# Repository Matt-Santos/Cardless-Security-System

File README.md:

# Cardless Security System
***
## Project Description
A **cardless security system** based on human **electro cardiogram (ECG) biometrics** that will be able to identify specified individuals, assess their authorization privileges and subsequently permit or deny access to
restricted areas. The entry regulation method is a custom designed electronic door locking
mechanism. Device is includes additional security features to prevent unauthorized entry. The unit
itself is battery operated with audio and visual indicators used to denote various system states.

## Goals and Objectives
1) Differentiate between individuals based on personal ECG signals
2) A secure mechanical locking system driven by an electric motor
## Brief Background
Most biometric identification devices currently in use throughout the world rely on either facial,
fingerprint, retina, or voice recognition systems. All of these authentication methods have been shown to
produce unique signatures that remain relatively consistent over time and are difficult to emulate with
the notable exception of voice based systems. Although obviously less secure the appeal of audio
biometric systems is driven primarily by its substantially lower implementation costs as opposed to the
other metrics which require sophisticated vision hardware. This desire for inexpensive biometric devices
has driven the search for alternative unique human signatures. Over the last few years electrocardiogram
(ECG) based recognition has shown potential. One of the advantages of this metric include the fact it is
an internal signal which is highly subject to personal health and mental state and is thus difficult to
procure from unwilling or deceased individuals. It is also fairly inexpensive to both capture and process
the ECG signals leading to a very high overall desirability. Research into this field is still being
conducted and very few viable commercial products are currently available.

## Final Result
An enclosed printed circuit board mounted alongside a custom electronic door locking mechanism.
The board is to include a built-in ECG acquisition system, audio and visual status indicators, as well as
the internal processing power required to perform biometric identification.

## Timeline
See [Gantt Chart](/documents/reports/Proposal/ProjectSchedule.pdf)

# Software Listing
* Git
* KiCAD
* GanttProject
* Latex (MiKTeX)
* Matlab (Octave)
* LTSpice

# Team Members
* Matthew Santos
* Robert Goleberski
* Zuwei Li
# Supervisors
* Dr. Emadi
* Dr. Mirhassani

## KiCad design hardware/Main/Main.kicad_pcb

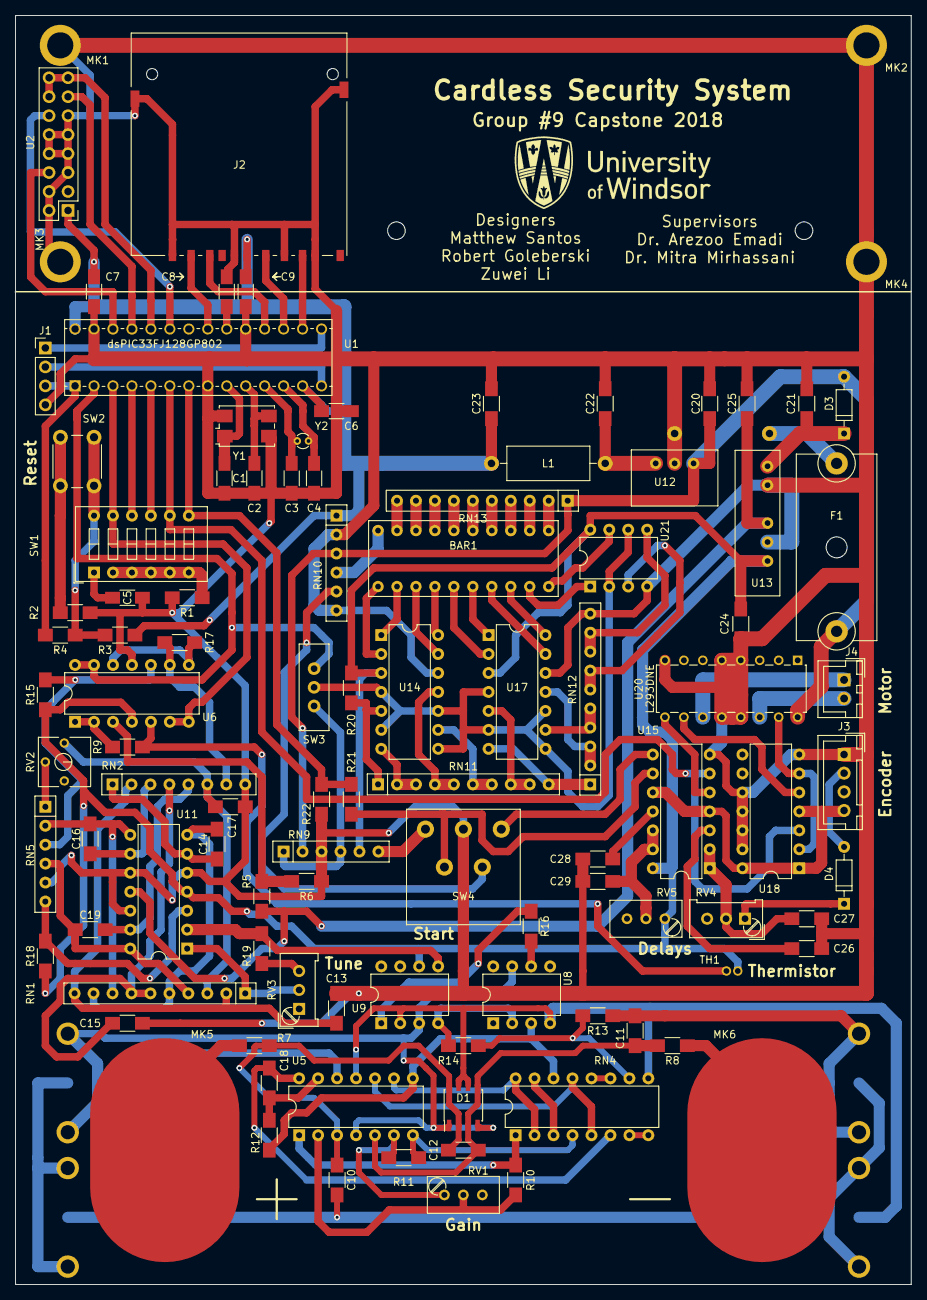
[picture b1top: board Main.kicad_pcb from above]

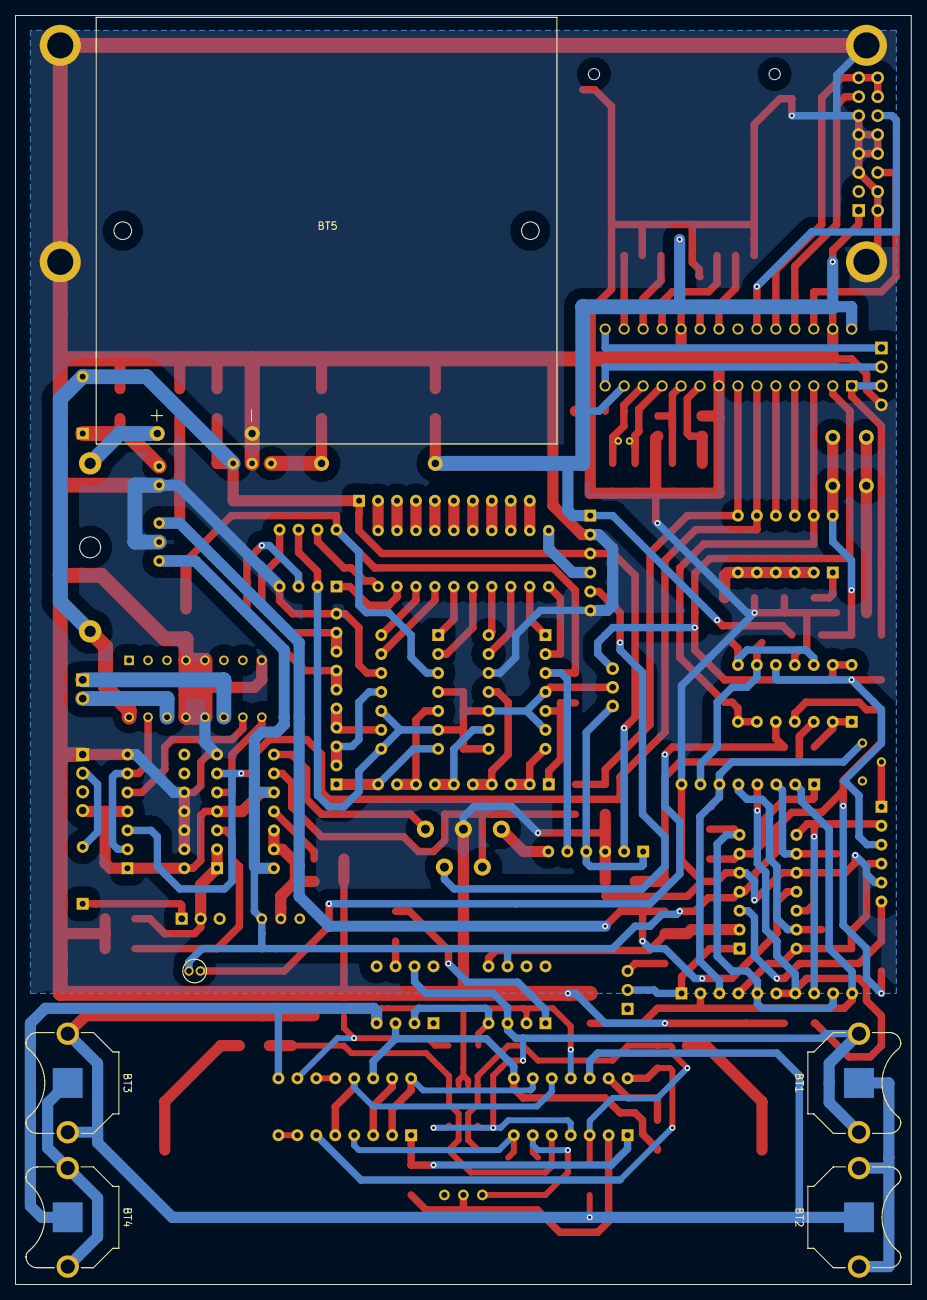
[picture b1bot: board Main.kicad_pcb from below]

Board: 2 copper layers, 120.0 x 170.0 mm, 108 parts (6 on the bottom side), 126 nets.

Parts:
BAR1: DC7G3HWA
BT1, BT2, BT3, BT4: Holder; Keystone_3001_1x12mm-CoinCell
BT5: Battery Holder; BH4AAPC
C1, C2: 27p; C1206C270F5GACTU
C3, C4: 15p; C1206C150J5GACTU
C5, C6, C7, C9: 0.1u; C1206C104K4RACTU
C8: 4.7u; F931C475KAA
C10, C11: 100p; R_1206_HandSoldering
C12: 1n; R_1206_HandSoldering
C13, C15, C17: 0.68u; R_1206_HandSoldering
C14, C16, C19: 0.068u; R_1206_HandSoldering
C18, C27, C29: 47u; R_1206_HandSoldering
C20, C22: 10u; R_1206_HandSoldering
C21, C24, C25: 4.7u; R_1206_HandSoldering
C23: 22u; R_1206_HandSoldering
C26, C28: 10n; R_1206_HandSoldering
D1: SMDA15TR; SOIC-8_3.9x4.9mm_Pitch1.27mm
D3, D4: 1N914; D_DO-35_SOD27_P7.62mm_Horizontal
F1: Fuse_Holder; 0031.8201
J1: ISCP; Pin_Header_Straight_1x04_Pitch2.54mm
J2: SD_Card; 145638009211859+
J3: EncoderHeader; JST_XH_B04B-XH-A_04x2.50mm_Straight
J4: MotorHeader; JST_XH_B02B-XH-A_02x2.50mm_Straight
L1: 10u; L_Axial_L11.0mm_D4.5mm_P15.24mm_Horizontal_Fastron_MECC
MK1, MK2, MK3, MK4: Mounting_Hole; MountingHole_2.5mm_Pad
MK5: Electrode_A; ECG_Pad
MK6: Electrode_B; ECG_Pad
R1, R4: 1k; R_1206_HandSoldering
R2, R16: 100; R_1206_HandSoldering
R3: 10k; R_1206_HandSoldering
R5: 5.6k; R_1206_HandSoldering
R6: 2.4k; R_1206_HandSoldering
R7, R8: 100k; R_1206_HandSoldering
R9: 3k; R_1206_HandSoldering
R10, R11, R19: 2k; R_1206_HandSoldering
R12: 82k; R_1206_HandSoldering
R13, R14: 1.5k; R_1206_HandSoldering
R15: 9k; R_1206_HandSoldering
R17: 40k; R_1206_HandSoldering
R18: 15k; R_1206_HandSoldering
R20: 18k; R_1206_HandSoldering
R21: 2.2k; R_1206_HandSoldering
R22: 3.3k; R_1206_HandSoldering
RN1: 3.3k; R_Array_SIP10
RN2: 10k; R_Array_SIP8
RN4: 10k; DIP-16_W7.62mm
RN5: 1k; R_Array_SIP6
RN9: 10k; R_Array_SIP6
RN10: 150; R_Array_SIP6
RN11, RN12: 2.7k; R_Array_SIP10
RN13: 150; R_Array_SIP10
RV1: 5kPOT; Potentiometer_Trimmer_Bourns_3296W
RV2: 3kPOT; 3362P-1-302LF
RV3: 2kPOT; Potentiometer_Trimmer_Bourns_PV36W
RV4: 100k POT; Potentiometer_Trimmer_Bourns_PV36W
RV5: 500k POT; Potentiometer_Trimmer_Bourns_3296W
SW1: SW_DIP_x06; 418117270906
SW2: Reset; TL1105F250Q
SW3: Bat-Test; EG1218
SW4: Start; UB15SKG035F-FF
TH1: Thermistor; DC103G9G
U1: dsPIC33FJ128GP802; DSPIC33FJ128GP802
U2: LCD_Header; Pin_Header_Straight_2x08_Pitch2.54mm
U5: LT1079CN; DIP-14_W7.62mm
U6, U11: TLC2264IN; DIP-14_W7.62mm
U8: LT1636; DIP-8_W7.62mm
U9: IL300; DIP-8_W7.62mm
U12: P7805-Q24-S3-S
U13: PDM1-S5-D5-S
U14, U17: LM339; DIP-14_W7.62mm
U15: NE556; DIP-14_W7.62mm
U18: 74HC74; DIP-14_W7.62mm
U20: L293DNE
U21: LM2903; DIP-8_W7.62mm
Y1: 10MHz; ABMM-10MHZ-B2-T
Y2: 32kHz; AB38T-32KHZ

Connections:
/AnalogFrontEnd/ECG_Signal: SW3.1, U1.2, U6.13, U6.14
/AnalogFrontEnd/GND_I: BT2.2, BT3.1, C10.2, C11.1, R13.2, U5.12
/AnalogFrontEnd/Isolator_Out: RN1.1, RV3.2, U11.1
/AnalogFrontEnd/Vcc_I: BT1.1, D1.1, D1.4, U5.4, U8.7, U9.3
/AnalogFrontEnd/Vee_I: BT4.2, D1.6, D1.7, RN4.9, U5.11, U8.4, U9.2
/MPU/AUX1: SW1.11, U1.3, U6.6, U6.7
/MPU/AUX2: SW1.10, U1.4
/MPU/AUX3: SW1.9, U1.5
/MPU/AUX4: SW1.8, U1.6, U15.6, U18.3
/MPU/LCD_CLK: U1.23, U2.12
/MPU/LCD_CS: U1.26, U2.6
/MPU/LCD_MISO: U1.25, U2.13
/MPU/LCD_MOSI: U1.24, U2.14, U2.15, U2.16
/MPU/PGC: J1.1, U1.15
/MPU/PGD: J1.2, U1.14
/MPU/PG_MCLR: J1.3, R4.1, U1.1
/MPU/SD_CLK: J2.5, U1.17
/MPU/SD_CS: J2.1, U1.21
/MPU/SD_MISO: J2.7, U1.16
/MPU/SD_MOSI: J2.2, U1.18
/MPU/START: R21.1, R22.2, SW1.7, U1.7
/PowerSystem/3.3V: C6.2, C7.1, C9.1, C23.2, J2.4, L1.2, R3.1, RN10.1, U1.13, U1.28, U2.1
/PowerSystem/6V: C20.1, D3.2, F1.1, RN9.2, RN10.3, RN13.1, U12.1, U20.16
/PowerSystem/-5V: C25.2, R5.1, U11.11, U13.3
/PowerSystem/EncoderB: D4.2, J3.2
/PowerSystem/L1: BAR1.11, U14.2
/PowerSystem/L2: BAR1.12, U14.1
/PowerSystem/L3: BAR1.13, U14.13
/PowerSystem/L4: BAR1.14, U14.14
/PowerSystem/L5: BAR1.15, U17.2
/PowerSystem/L6: BAR1.16, U17.1
/PowerSystem/L7: BAR1.17, U17.13
/PowerSystem/L8: BAR1.18, U17.14
/PowerSystem/L9: BAR1.19, U21.1
/PowerSystem/L10: BAR1.20, U21.7
/PowerSystem/Vm+: J4.2, U20.14
/PowerSystem/Vm-: J4.1, U20.11
/StartRelay/TimedStart: R21.2, SW4.4, U15.9
GND: BT5.2, C1.1, C2.1, C3.1, C4.1, C5.2, C6.1, C7.2, C8.2, C9.2, C13.2, C15.2, C17.2, C20.2, C21.1, C22.1, C23.1, C24.2, C25.1, C26.2, C27.2, C28.2, C29.2, J1.4, J2.3, J2.6, J2.8, J2.9, J2.12, J2.13, J3.1, MK1.1, MK2.1, MK3.1, MK4.1, R1.2, R2.2, R6.2, R22.1, RN2.8, RN5.5, RN9.3, RN10.2, RN10.6, RN12.10, SW4.2, U1.8, U1.19, U1.27, U2.2, U2.4, U2.5, U2.7, U2.8, U2.9, U2.10, U2.11, U6.11, U11.5, U11.10, U11.12, U12.2, U13.2, U13.4, U14.12, U15.7, U17.12, U18.7, U18.10, U18.11, U18.12, U18.13, U20.4, U20.5, U20.8, U20.12, U20.13, U21.4, Y1.2, Y1.4
unnamed: BAR1.1, RN13.2
unnamed: BAR1.2, RN13.3
unnamed: BAR1.3, RN13.4
unnamed: BAR1.4, RN13.5
unnamed: BAR1.5, RN13.6
unnamed: BAR1.6, RN13.7
unnamed: BAR1.7, RN13.8
unnamed: BAR1.8, RN13.9
unnamed: BAR1.9, RN13.10
unnamed: BAR1.10, RN10.4
unnamed: BT1.2, BT2.1
unnamed: BT3.2, BT4.1
unnamed: BT5.1, F1.2
unnamed: C1.2, U1.9, Y1.1
unnamed: C2.2, U1.10, Y1.3
unnamed: C3.2, U1.11, Y2.1
unnamed: C4.2, U1.12, Y2.2
unnamed: C5.1, SW1.1
unnamed: C8.1, U1.20
unnamed: C10.1, C12.1, D1.2, D1.8, R7.1, U5.3
unnamed: C11.2, C12.2, D1.3, D1.5, R8.1, U5.5
unnamed: C13.1, RN1.2, RN1.10, RN2.2
unnamed: C14.1, RN2.1, U11.6
unnamed: C14.2, RN1.5, RN1.9, U11.7
unnamed: C15.1, RN1.6, RN1.7, RN2.4
unnamed: C16.1, RN2.3, U11.9
unnamed: C16.2, RN1.8, RN5.2, U11.8
unnamed: C17.1, RN1.3, RN2.6, RV2.1
unnamed: C18.1, RN4.6, U5.14
unnamed: C18.2, R12.2, U5.13
unnamed: C19.1, RN2.5, U11.13
unnamed: C19.2, RN1.4, RN5.4, U11.14
unnamed: C21.2, D3.1, U13.1
unnamed: C22.2, L1.1, U12.3
unnamed: C26.1, U15.3
unnamed: C27.1, RV4.2, U15.1, U15.2
unnamed: C28.1, U15.11
unnamed: C29.1, RV5.2, U15.12, U15.13
unnamed: D4.1, RV4.1
unnamed: MK5.1, R7.2
unnamed: MK6.1, R8.2
unnamed: R1.1, SW1.2, SW1.3, SW1.4, SW1.5, SW1.6
unnamed: R2.1, SW2.1
unnamed: R3.2, R4.2, SW1.12, SW2.2
unnamed: R5.2, R6.1, U6.3
unnamed: R9.1, U6.1, U6.2
unnamed: R9.2, TH1.1, U6.5
unnamed: R10.1, RV1.2, U5.2
unnamed: R10.2, RN4.1, U5.1
unnamed: R11.1, RN4.4, U5.7
unnamed: R11.2, RV1.1, U5.6
unnamed: R12.1, RN4.14, U5.8, U8.3
unnamed: R13.1, R14.1, RN4.10
unnamed: R14.2, U8.2, U9.4
unnamed: R15.1, RN5.3, U6.10
unnamed: R16.1, U9.1
unnamed: R16.2, U8.6
unnamed: R17.1, RN2.7, U6.9
unnamed: R17.2, U6.8, U6.12
unnamed: R18.1, RN5.6, U11.3
unnamed: R19.1, RV3.3
unnamed: R19.2, U9.5, U11.2
unnamed: R20.1, RN11.1, U14.5
unnamed: RN4.7, RN4.8
unnamed: RN4.11, RN4.12
unnamed: RN4.5, RN4.13, U5.10
unnamed: RN4.3, RN4.15
unnamed: RN4.2, RN4.16, U5.9
unnamed: RN5.1, RV2.2
unnamed: RN9.1, RN9.4, SW3.3
unnamed: RN9.6, SW4.3
unnamed: RN10.5, SW4.5
unnamed: RN11.2, RN11.3, U14.7
unnamed: RN11.4, RN11.5, U14.11
unnamed: RN11.6, RN11.7, U14.9
unnamed: RN11.8, RN11.9, U17.5
unnamed: RN11.10, RN12.1, U17.7
unnamed: RN12.2, RN12.3, U17.11
unnamed: RN12.4, RN12.5, U17.9
unnamed: RN12.6, RN12.7, U21.3
unnamed: RN12.8, RN12.9, U21.5
unnamed: SW3.2, U14.4, U14.6, U14.8, U14.10, U17.4, U17.6, U17.8, U17.10, U21.2, U21.6
unnamed: SW4.1, U15.8
unnamed: U15.5, U20.9
unnamed: U18.2, U18.6, U20.15
unnamed: U18.5, U20.10
VCC: C24.1, J3.4, R15.2, R18.2, R20.2, RN9.5, RV5.1, TH1.2, U6.4, U9.6, U11.4, U13.5, U14.3, U15.4, U15.10, U15.14, U17.3, U18.1, U18.4, U18.14, U21.8

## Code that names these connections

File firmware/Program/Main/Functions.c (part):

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  //External Interrupts (Inputs)
  RPINR0bits.INT1R = 3;     //RP3    => INT-1 (START)
  //Digital Outputs (Outputs)
  RPOR0bits.RP0R = 0;       //RP0    => RP0   (AUX2)
  RPOR0bits.RP1R = 0;       //RP1    => RP1   (AUX3)
  RPOR1bits.RP2R = 0;       //RP2    => RP2   (AUX4)
  RPOR5bits.RP11R = 0;      //RP11   => RP11  (AUX5)
  //ADC-1 Configuration with DMA0 (CH0=AN1,CH1=AN0)
  AD1CON1bits.ADON = 0;     //Turn OFF ADC-1
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
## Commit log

2024-12-31 feat: add primary content
2025-01-09 feat: update project README
2025-01-10 fix: remove redundant gerber pdfs
2025-01-10 fix: error with pcb
